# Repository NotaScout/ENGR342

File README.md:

// ENGR 342

// It be a ESP-32 S2 based Microcontroller with Wifi-antenna, Innit?

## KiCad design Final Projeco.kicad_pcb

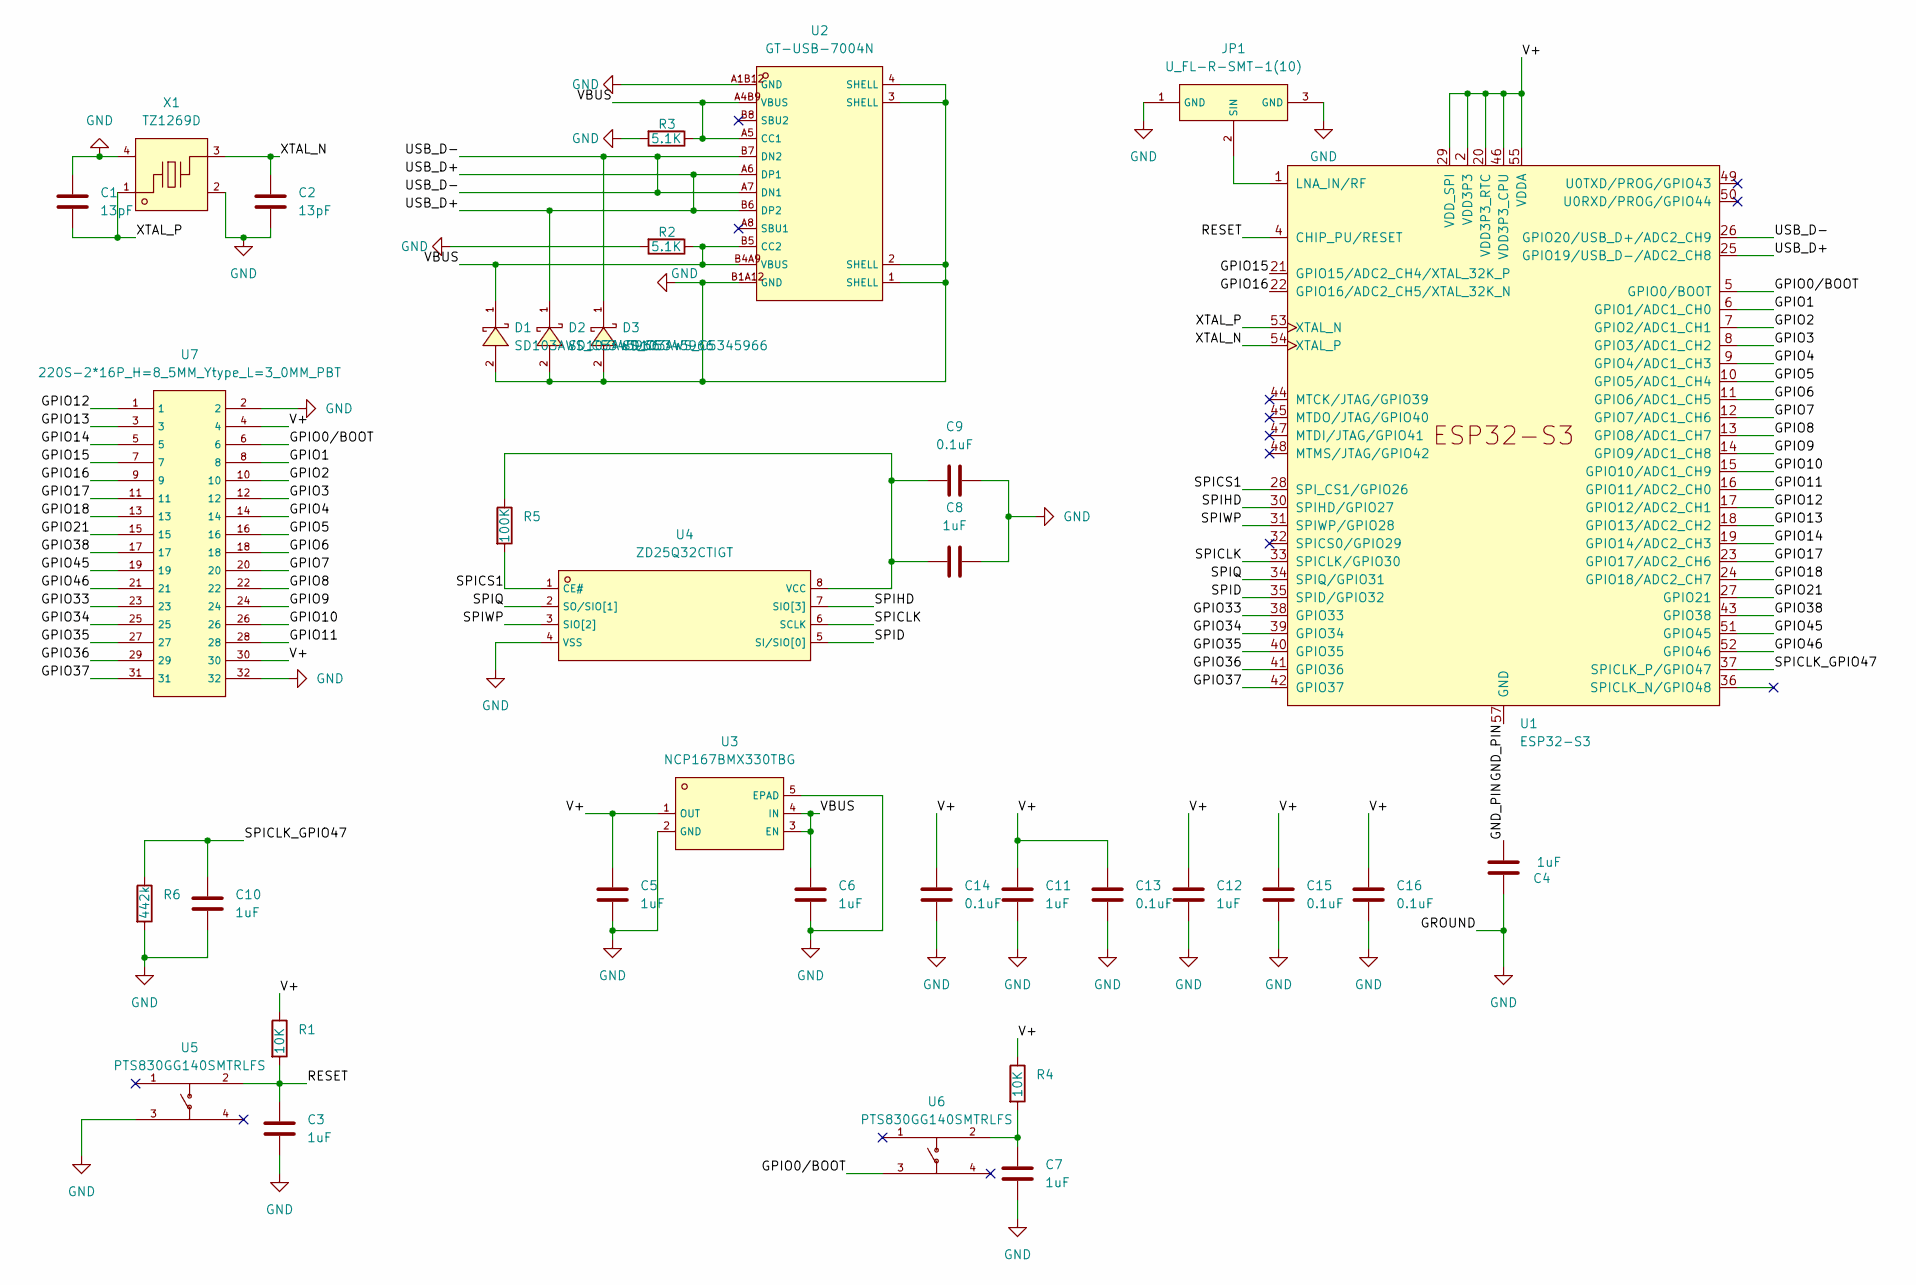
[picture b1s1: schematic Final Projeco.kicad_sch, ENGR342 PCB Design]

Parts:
C1, C2: 13pF; C_0402_1005Metric; LCSC C161528
C3, C4, C5, C6, C7, C8, C10, C11, C12: 1uF; C_0402_1005Metric; LCSC C29266
C9, C13, C14, C15, C16: 0.1uF; C_0402_1005Metric; LCSC C307331
D1, D2, D3: SD103AWS_C5345966; SOD-323_L1.7-W1.3-LS2.5-RD; LCSC C5345966
JP1: U_FL-R-SMT-1(10); ANT-SMD_UFL-R-SMT-1-10; LCSC C88373
R1, R4: 10K; R_0402_1005Metric; LCSC C25744
R2, R3: 5.1K; R_0402_1005Metric; LCSC C14677
R5: 100K; R_0402_1005Metric; LCSC C25741
R6: 442k; R_0402_1005Metric; LCSC C3016035
U1: ESP32-S3; QFN-56-1EP_7x7mm_P0.4mm_EP5.6x5.6mm; LCSC C2913194
U2: GT-USB-7004N; USB-C-SMD_GT-USB-7004; LCSC C2848971
U3: NCP167BMX330TBG; XDFN-4_L1.0-W1.0-P0.65-BL-EP; LCSC C892227
U4: ZD25Q32CTIGT; SOP-8_L4.9-W3.9-P1.27-LS6.0-BL; LCSC C261881
U5, U6: PTS830GG140SMTRLFS; KEY-SMD_4P-L3.1-W2.6_PTS830GG140SMTRLFS; LCSC C221902
U7: 220S-2*16P_H=8_5MM_Ytype_L=3_0MM_PBT; HDR-TH_32P-P2.54-V-F-R2-C16-S2.54; LCSC C115248
X1: TZ1269D; CRYSTAL-SMD_4P-L2.0-W1.6-BL-A; LCSC C501798

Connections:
/GND_PIN: C4.1, U1.57 (GND)
/GPIO0/BOOT: U1.5 (GPIO0/BOOT), U6.3, U7.6
/GPIO1: U1.6 (GPIO1/ADC1_CH0), U7.8
/GPIO2: U1.7 (GPIO2/ADC1_CH1), U7.10
/GPIO3: U1.8 (GPIO3/ADC1_CH2), U7.12
/GPIO4: U1.9 (GPIO4/ADC1_CH3), U7.14
/GPIO5: U1.10 (GPIO5/ADC1_CH4), U7.16
/GPIO6: U1.11 (GPIO6/ADC1_CH5), U7.18
/GPIO7: U1.12 (GPIO7/ADC1_CH6), U7.20
/GPIO8: U1.13 (GPIO8/ADC1_CH7), U7.22
/GPIO9: U1.14 (GPIO9/ADC1_CH8), U7.24
/GPIO10: U1.15 (GPIO10/ADC1_CH9), U7.26
/GPIO11: U1.16 (GPIO11/ADC2_CH0), U7.28
/GPIO12: U1.17 (GPIO12/ADC2_CH1), U7.1
/GPIO13: U1.18 (GPIO13/ADC2_CH2), U7.3
/GPIO14: U1.19 (GPIO14/ADC2_CH3), U7.5
/GPIO15: U1.21 (GPIO15/ADC2_CH4/XTAL_32K_P), U7.7
/GPIO16: U1.22 (GPIO16/ADC2_CH5/XTAL_32K_N), U7.9
/GPIO17: U1.23 (GPIO17/ADC2_CH6), U7.11
/GPIO18: U1.24 (GPIO18/ADC2_CH7), U7.13
/GPIO21: U1.27 (GPIO21), U7.15
/GPIO33: U1.38 (GPIO33), U7.23
/GPIO34: U1.39 (GPIO34), U7.25
/GPIO35: U1.40 (GPIO35), U7.27
/GPIO36: U1.41 (GPIO36), U7.29
/GPIO37: U1.42 (GPIO37), U7.31
/GPIO38: U1.43 (GPIO38), U7.17
/GPIO45: U1.51 (GPIO45), U7.19
/GPIO46: U1.52 (GPIO46), U7.21
/RESET: C3.1, R1.2, U1.4 (CHIP_PU/RESET), U5.2
/SPICLK: U1.33 (SPICLK/GPIO30), U4.6 (SCLK)
/SPICLK_GPIO47: C10.1, R6.1, U1.37 (SPICLK_P/GPIO47)
/SPICS1: R5.2, U1.28 (SPI_CS1/GPIO26), U4.1 (CE#)
/SPID: U1.35 (SPID/GPIO32), U4.5 (SI/SIO[0])
/SPIHD: U1.30 (SPIHD/GPIO27), U4.7 (SIO[3])
/SPIQ: U1.34 (SPIQ/GPIO31), U4.2 (SO/SIO[1])
/SPIWP: U1.31 (SPIWP/GPIO28), U4.3 (SIO[2])
/USB_D+: D2.1 (K), U1.25 (GPIO19/USB_D-/ADC2_CH8), U2.A6 (DP1), U2.B6 (DP2)
/USB_D-: D3.1 (K), U1.26 (GPIO20/USB_D+/ADC2_CH9), U2.A7 (DN1), U2.B7 (DN2)
/VBUS: C6.1, D1.1 (K), R2.1, R3.1, U2.A4B9 (VBUS), U2.A5 (CC1), U2.B4A9 (VBUS), U2.B5 (CC2), U3.3 (EN), U3.4 (IN)
/XTAL_N: C2.1, U1.54 (XTAL_P), X1.3
/XTAL_P: C1.2, U1.53 (XTAL_N), X1.1
GND: C1.1, C2.2, C3.2, C4.2, C5.2, C6.2, C7.2, C8.2, C9.2, C10.2, C11.2, C12.2, C13.1, C14.1, C15.1, C16.1, D1.2 (A), D2.2 (A), D3.2 (A), JP1.1 (GND), JP1.3 (GND), R2.2, R3.2, R6.2, U2.1 (SHELL), U2.2 (SHELL), U2.3 (SHELL), U2.4 (SHELL), U2.A1B12 (GND), U2.B1A12 (GND), U3.2 (GND), U3.5 (EPAD), U4.4 (VSS), U5.3, U7.2, U7.32, X1.2 (GND), X1.4 (GND)
unnamed: C7.1, R4.2, U6.2
unnamed: JP1.2 (SIN), U1.1 (LNA_IN/RF)
unnamed: C8.1, C9.1, R5.1, U4.8 (VCC)
VDD3P3: C5.1, C11.1, C12.1, C13.2, C14.2, C15.2, C16.2, R1.1, R4.1, U1.2 (VDD3P3), U1.3 (VDD3P3), U1.20 (VDD3P3_RTC), U1.29 (VDD_SPI), U1.46 (VDD3P3_CPU), U1.55 (VDDA), U1.56 (VDDA), U3.1 (OUT), U7.4, U7.30

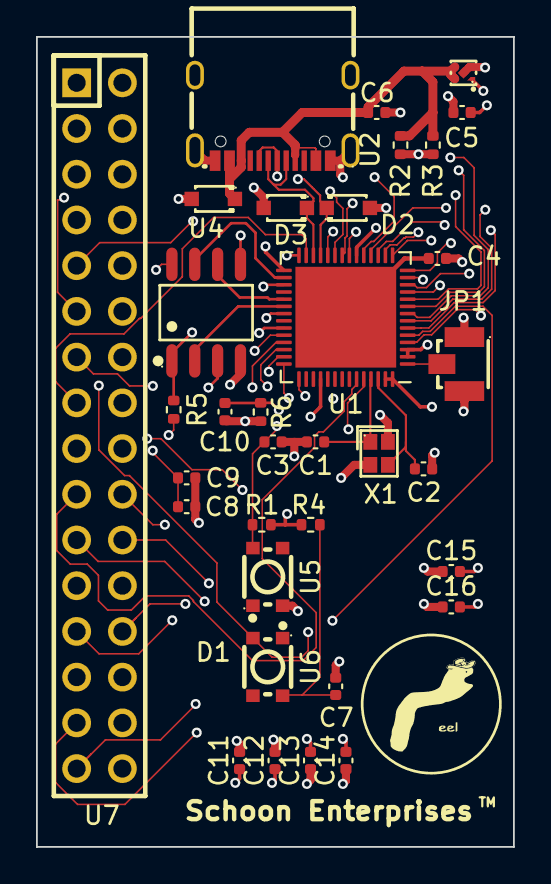
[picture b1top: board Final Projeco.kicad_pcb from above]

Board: 6 copper layers, 26.5 x 45.0 mm, 34 parts (0 on the bottom side), 47 nets.

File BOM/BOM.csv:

"Reference","Value","Datasheet","Footprint","Qty","DNP","LCSC"
"C1,C2","13pF","~","Capacitor_SMD:C_0402_1005Metric","2","","C161528"
"C3,C4,C5,C6,C7,C8,C10","1uF","~","Capacitor_SMD:C_0402_1005Metric","7","","C29266"
"C9","0.1uF","~","Capacitor_SMD:C_0402_1005Metric","1","","C307331"
"D1,D2,D3","SD103AWS_C5345966","https://img.jlc.com/pdf/applyPasteComponent/2021-04-20/39036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","jlc:SOD-323_L1.7-W1.3-LS2.5-RD","3","","C5345966"
"JP1","U_FL-R-SMT-1(10)","https://item.szlcsc.com/89552.html","jlc:ANT-SMD_UFL-R-SMT-1-10","1","","C88373"
"R1,R4","10K","~","Resistor_SMD:R_0402_1005Metric","2","","C25744"
"R2,R3","5.1K","~","Resistor_SMD:R_0402_1005Metric","2","","C14677"
"R5","100K","~","Resistor_SMD:R_0402_1005Metric","1","","C25741"
"R6","442k","~","Resistor_SMD:R_0402_1005Metric","1","","C3016035"
"U1","ESP32-S3","https://www.espressif.com/sites/default/files/documentation/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","Package_DFN_QFN:QFN-56-1EP_7x7mm_P0.4mm_EP5.6x5.6mm","1","","C2913194"
"U2","GT-USB-7004N","https://atta.szlcsc.com/upload/public/pdf/source/20210507/C2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","jlc:USB-C-SMD_GT-USB-7004","1","","C2848971"
"U3","NCP167BMX330TBG","https://item.szlcsc.com/196276.html","jlc:XDFN-4_L1.0-W1.0-P0.65-BL-EP","1","","C892227"
"U4","LY68L6400SLIT","https://item.szlcsc.com/383602.html","jlc:SOP-8_L4.9-W3.9-P1.27-LS6.0-BL","1","","C261881"
"U5,U6","PTS830GG140SMTRLFS","https://atta.szlcsc.com/upload/public/pdf/source/20220328/BD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","jlc:KEY-SMD_4P-L3.1-W2.6_PTS830GG140SMTRLFS","2","","C221902"
"U7","220S-2*16P_H=8_5MM_Ytype_L=3_0MM_PBT","https://item.szlcsc.com/2776437.html?ref=editor&logined=true","jlc:HDR-TH_32P-P2.54-V-F-R2-C16-S2.54","1","","C115248"
"X1","TZ1269D","https://atta.szlcsc.com/upload/public/pdf/source/20210612/25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","jlc:CRYSTAL-SMD_4P-L2.0-W1.6-BL-A","1","","C501798"

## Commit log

2024-04-12 -Added Project Files
2024-04-12 -Updated some parts -added datasheets for possible Antanneax -design is structurally complete... I think?
2024-04-15 -Cleaned up schematic (Nets) -Added more Deditated wam
2024-04-15 -USE IPEX 2.4 GHz Antenna
2024-04-19 -Added some Headers
    -Added Headers
    -TODO (chore) (top priority):
    - relabel EVERYTHING with net class (line) NOT directive (circle)
    - get layout fixed
2024-04-19 Create README.md
    one of the readme to ever exist
2024-04-22 Fixed all the traces to connect to each other :-|
2024-04-22 Fixed some stuff
    -added diff pair net rules
    -added base net rules
    -added zmatch net rules
2024-04-24 Started Routing
2024-04-25 stuff
2024-04-26 Final build init commit
    -No DRC errors,
    -All routed
2024-04-26 -Final Files Part II
    Generated BOM, CPL, & GBRs,
    TODO;
    -Remove RAM & all wires related
2024-04-26 -Final Draft Submission mk2
    -Added bypass caps across 3.3 & GND to make signal less ripple-y
    -added component to replace SRAM chip:
    https://jlcpcb.com/partdetail/Zetta-ZD25Q32CTIGT/C3029778
2024-04-27 Create Repoert
2024-05-13 -Picutre
    - + Added Pictures of printed boards.
2024-05-13 Addded depictions of our board
